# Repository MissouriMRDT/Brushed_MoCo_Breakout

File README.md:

# Brushed_MoCo_Breakout
Breakout board for custom brushed DC motor controllers

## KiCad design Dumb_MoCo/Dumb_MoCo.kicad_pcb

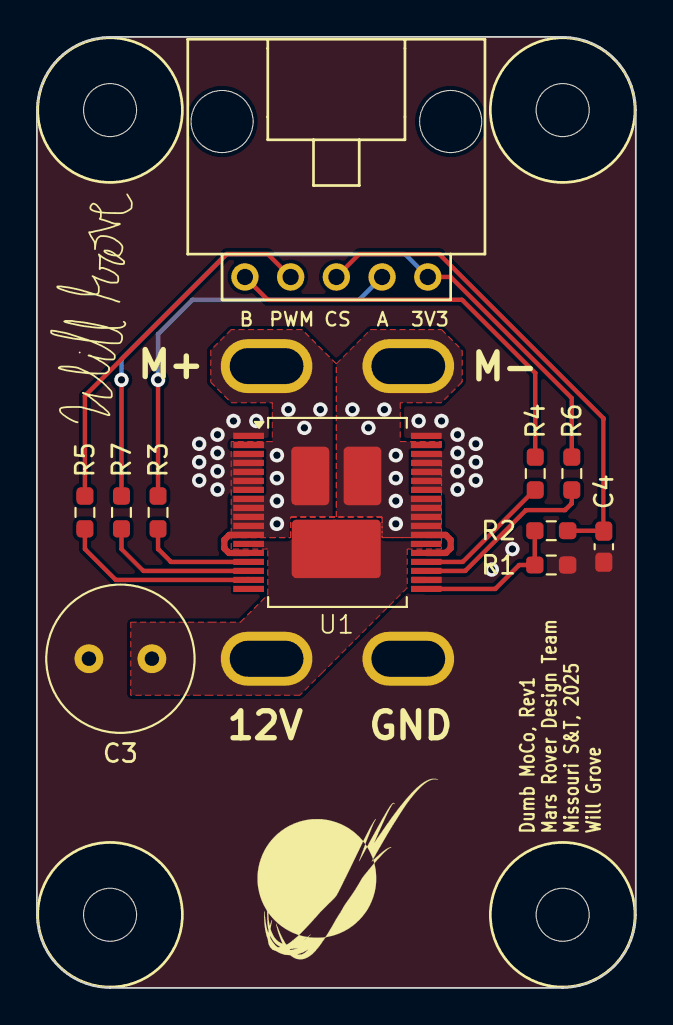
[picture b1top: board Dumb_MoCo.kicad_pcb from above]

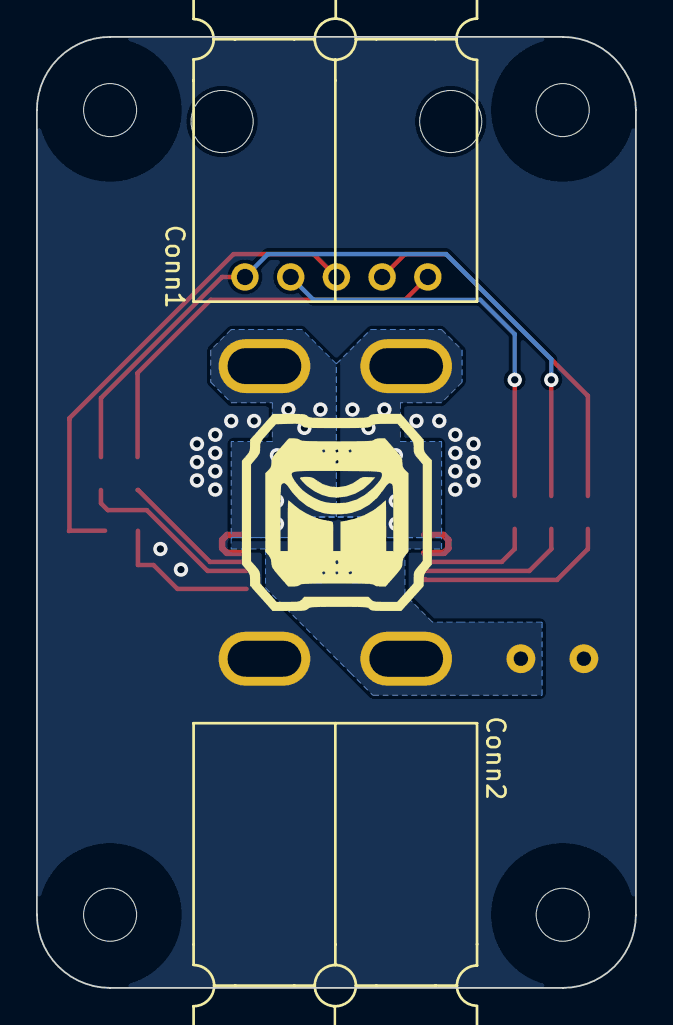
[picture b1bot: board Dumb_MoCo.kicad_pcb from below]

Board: 2 copper layers, 33.3 x 52.8 mm, 17 parts (2 on the bottom side), 15 nets.

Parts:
C3: 330uF; C_Radial_D8.0mm_H11.5mm_P3.50mm
C4: 33nF; C_0603_1608Metric_Pad1.08x0.95mm_HandSolder
Conn1, Conn2: AndersonPP; Square_Anderson_2_H_Side_By_Side
Conn3: Molex_SL_05; MOLEX_SL_05_Horizontal
H1, H2, H3, H4: MountingHole; 4_40_Hole
R1: 1.5k; R_0603_1608Metric_Pad0.98x0.95mm_HandSolder
R2: 10k; R_0603_1608Metric_Pad0.98x0.95mm_HandSolder
R3, R4, R5: 1k; R_0603_1608Metric_Pad0.98x0.95mm_HandSolder
R6, R7: 3.3k; R_0603_1608Metric_Pad0.98x0.95mm_HandSolder
U1: VNH5050A-E; ST_PowerSSO-36_TP

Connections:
+3V3: Conn3.5, R6.1, R7.1
+12V: C3.1, Conn2.2 (V+Log), U1.13 (VCC), U1.24 (VCC)
CS: C4.2, Conn3.3, R2.2
GND: C3.2, C4.1, Conn2.1 (GND), R1.2, U1.1 (GND_A), U1.3 (GND_A), U1.4 (GND_A), U1.5 (GND_A), U1.6 (GND_A), U1.7 (GND_A), U1.20 (CS_DIS), U1.30 (GND_B), U1.31 (GND_B), U1.32 (GND_B), U1.33 (GND_B), U1.34 (GND_B), U1.36 (GND_B)
IN_A: Conn3.4, R3.1
IN_B: Conn3.1, R4.1
unnamed: Conn1.1 (GND), U1.2 (OUT_A), U1.8 (OUT_A), U1.9 (OUT_A), U1.10 (OUT_A), U1.11 (OUT_A), U1.12 (OUT_A), U1.14 (OUT_A)
unnamed: Conn1.2 (V+Log), U1.23 (OUT_B), U1.25 (OUT_B), U1.26 (OUT_B), U1.27 (OUT_B), U1.28 (OUT_B), U1.29 (OUT_B), U1.35 (OUT_B)
unnamed: R1.1, R2.1, U1.19 (CS)
unnamed: R7.2, U1.16 (DIAG_A/EN_A)
unnamed: R6.2, U1.21 (DIAG_B/EN_B)
unnamed: R3.2, U1.15 (INA)
unnamed: R4.2, U1.22 (INB)
unnamed: R5.2, U1.17 (PWM)
PWM: Conn3.2, R5.1

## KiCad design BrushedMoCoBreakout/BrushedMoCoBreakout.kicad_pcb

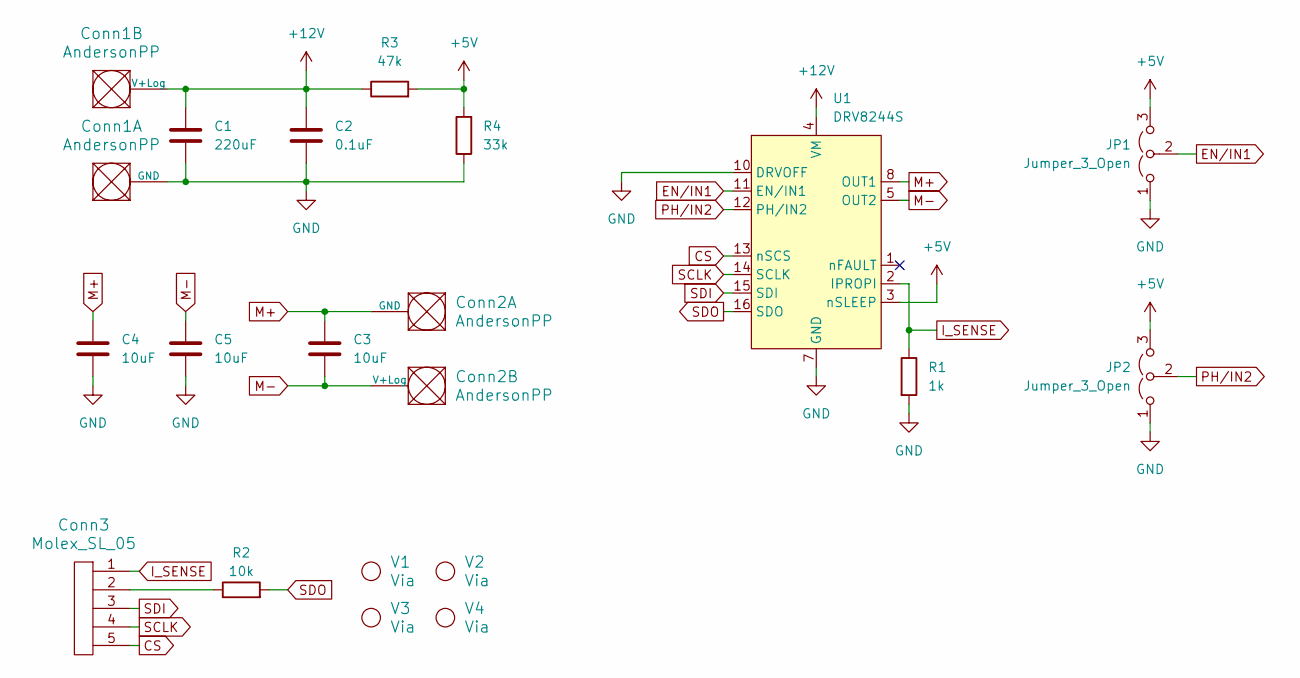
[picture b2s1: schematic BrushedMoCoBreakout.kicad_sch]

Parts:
C1: 220uF; CP_Radial_D6.3mm_P2.50mm
C2: 0.1uF; C_0603_1608Metric_Pad1.08x0.95mm_HandSolder
C3, C4, C5: 10uF; C_0603_1608Metric_Pad1.08x0.95mm_HandSolder
Conn1, Conn2: AndersonPP; Square_Anderson_2_H_Stacked_PV
Conn3: Molex_SL_05; MOLEX_SL_05_Horizontal
JP1, JP2: Jumper_3_Open; PinHeader_1x03_P1.00mm_Vertical
R1: 1k; R_0603_1608Metric_Pad0.98x0.95mm_HandSolder
R2: 10k; R_0603_1608Metric_Pad0.98x0.95mm_HandSolder
R3: 47k; R_0603_1608Metric_Pad0.98x0.95mm_HandSolder
R4: 33k; R_0603_1608Metric_Pad0.98x0.95mm_HandSolder
U1: DRV8244S; VQFN-HR-16_4.0mmx7.0mm_ThermalVias
V1, V2, V3, V4: Via; 4_40_Hole

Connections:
+5V: JP1.3 (B), JP2.3 (B), R3.2, R4.2, U1.3 (nSLEEP)
+12V: C1.1, C2.1, Conn1.2 (V+Log), R3.1, U1.4 (VM)
CS: Conn3.5, U1.13 (nSCS)
EN/IN1: JP1.2 (C), U1.11 (EN/IN1)
GND: C1.2, C2.2, C4.2, C5.2, Conn1.1 (GND), JP1.1 (A), JP2.1 (A), R1.2, R4.1, U1.7 (GND), U1.10 (DRVOFF)
I_SENSE: Conn3.1, R1.1, U1.2 (IPROPI)
M+: C3.1, C4.1, Conn2.1 (GND), U1.8 (OUT1), U1.9 (OUT1)
M-: C3.2, C5.1, Conn2.2 (V+Log), U1.5 (OUT2), U1.6 (OUT2)
unnamed: Conn3.2, R2.1
PH/IN2: JP2.2 (C), U1.12 (PH/IN2)
SCLK: Conn3.4, U1.14 (SCLK)
SDI: Conn3.3, U1.15 (SDI)
SDO: R2.2, U1.16 (SDO)

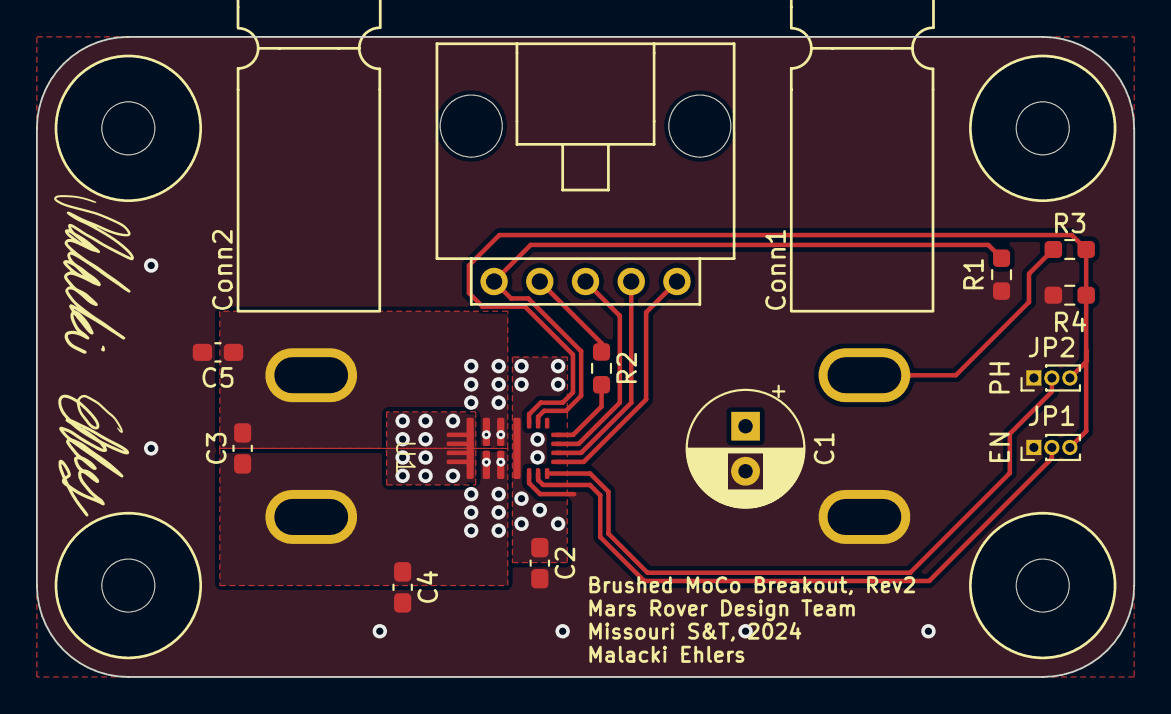
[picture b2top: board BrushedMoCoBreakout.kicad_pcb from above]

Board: 2 copper layers, 61.0 x 35.6 mm, 19 parts (0 on the bottom side), 13 nets.

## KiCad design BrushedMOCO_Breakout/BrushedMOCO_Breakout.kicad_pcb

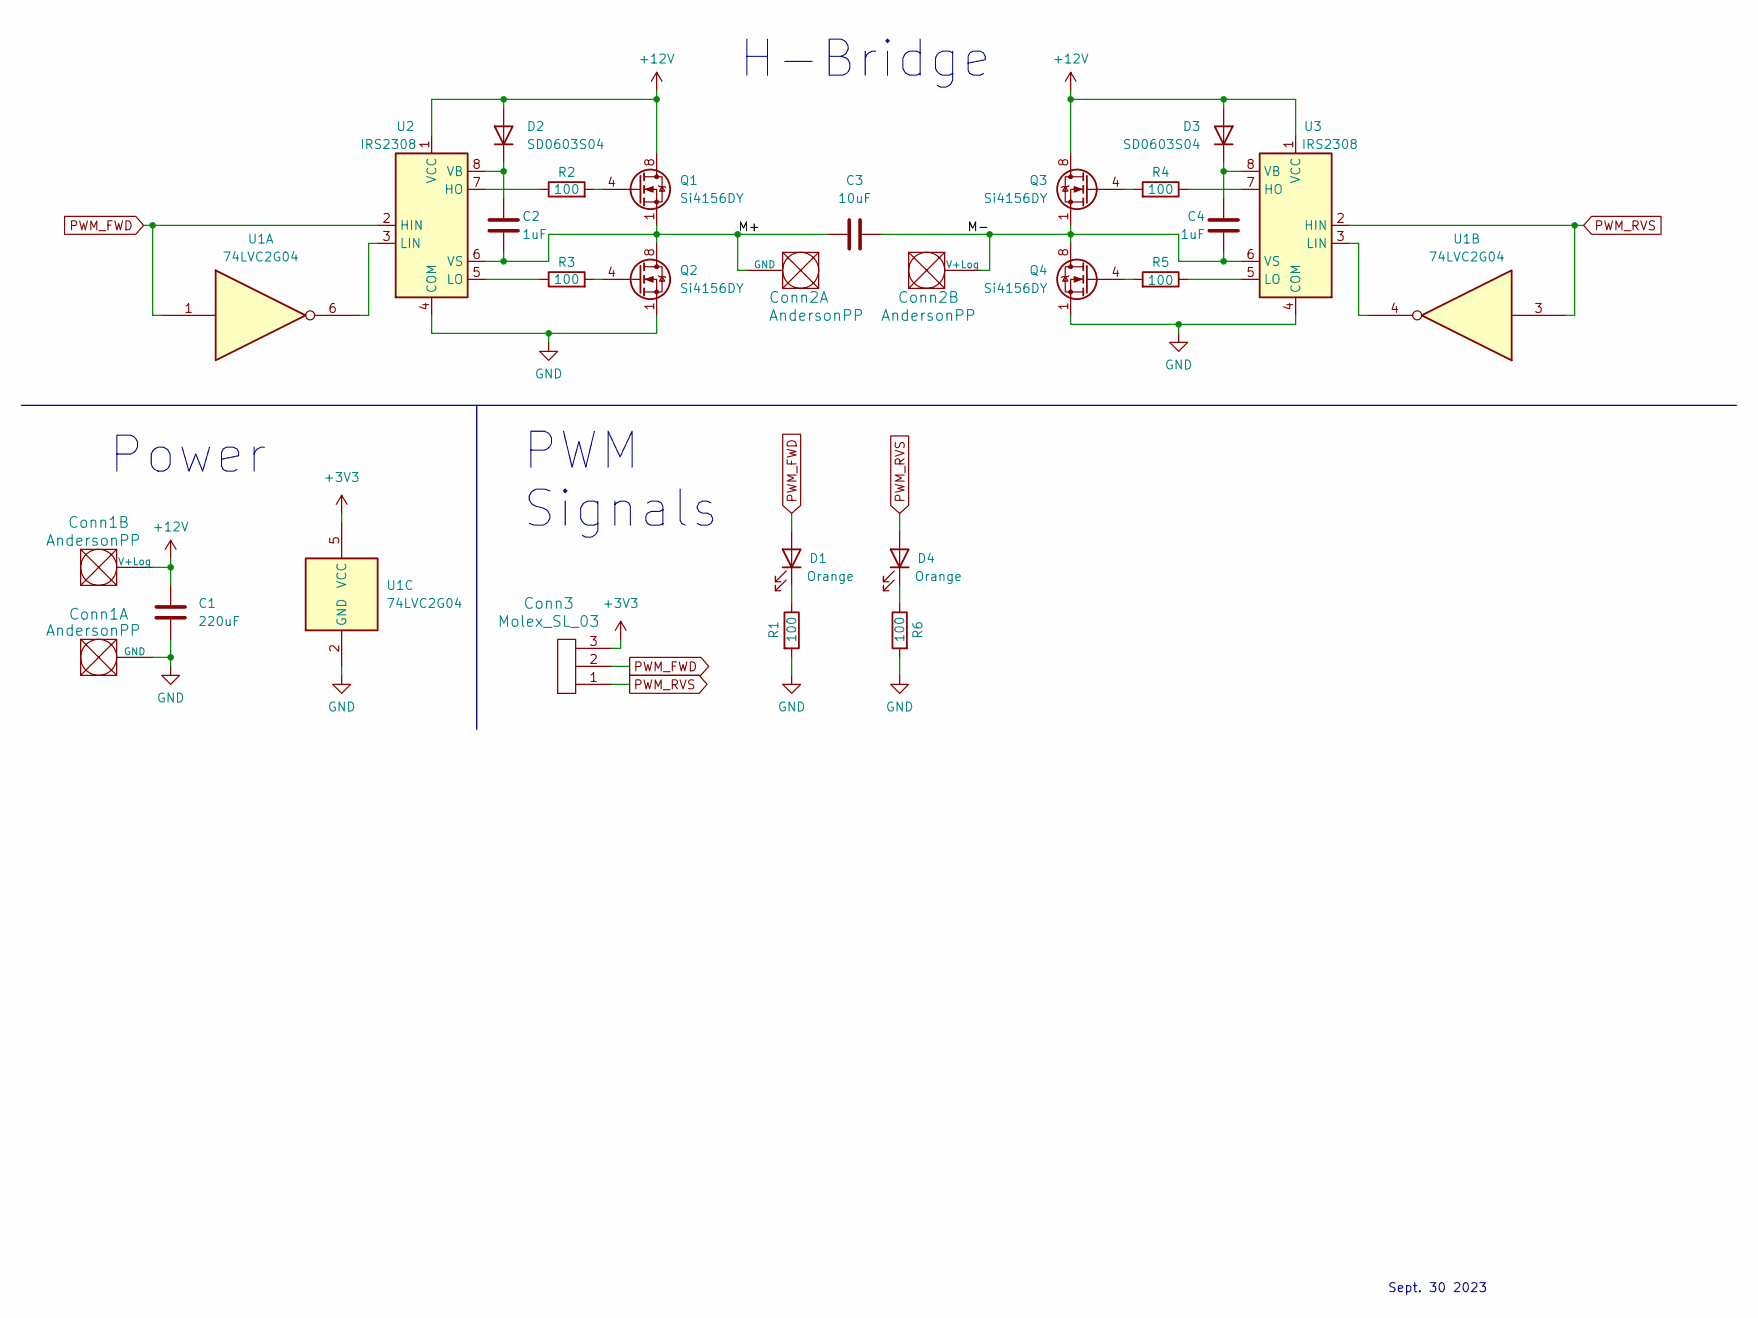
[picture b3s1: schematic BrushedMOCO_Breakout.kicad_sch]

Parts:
C1: 220uF; CP_Radial_D6.3mm_P2.50mm
C2, C4: 1uF; C_0603_1608Metric_Pad1.08x0.95mm_HandSolder
C3: 10uF; C_0603_1608Metric_Pad1.08x0.95mm_HandSolder
Conn1, Conn2: AndersonPP; Square_Anderson_2_H_Side_By_Side
Conn3: Molex_SL_03; MOLEX_SL_03_Horizontal
D1, D4: Orange; LED_0603_1608Metric_Pad1.05x0.95mm_HandSolder
D2, D3: SD0603S04; D_0603_1608Metric_Pad1.05x0.95mm_HandSolder
Q1, Q2, Q3, Q4: Si4156DY; SOIC-8_3.9x4.9mm_P1.27mm
R1, R2, R3, R4, R5, R6: 100; R_0603_1608Metric_Pad0.98x0.95mm_HandSolder
U1: 74LVC2G04; SOT-23-6_Handsoldering
U2, U3: IRS2308; SOIC-8_3.9x4.9mm_P1.27mm

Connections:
+3V3: Conn3.3, U1.5 (VCC)
+12V: C1.1, Conn1.2 (V+Log), D2.2 (A), D3.2 (A), Q1.5 (D), Q1.6 (D), Q1.7 (D), Q1.8 (D), Q3.5 (D), Q3.6 (D), Q3.7 (D), Q3.8 (D), U2.1 (VCC), U3.1 (VCC)
/M+: C2.2, C3.1, Conn2.1 (GND), Q1.1 (S), Q1.2 (S), Q1.3 (S), Q2.5 (D), Q2.6 (D), Q2.7 (D), Q2.8 (D), U2.6 (VS)
/M-: C3.2, C4.2, Conn2.2 (V+Log), Q3.1 (S), Q3.2 (S), Q3.3 (S), Q4.5 (D), Q4.6 (D), Q4.7 (D), Q4.8 (D), U3.6 (VS)
GND: C1.2, Conn1.1 (GND), Q2.1 (S), Q2.2 (S), Q2.3 (S), Q4.1 (S), Q4.2 (S), Q4.3 (S), R1.2, R6.2, U1.2 (GND), U2.4 (COM), U3.4 (COM)
unnamed: D1.1 (K), R1.1
unnamed: C2.1, D2.1 (K), U2.8 (VB)
unnamed: C4.1, D3.1 (K), U3.8 (VB)
unnamed: D4.1 (K), R6.1
unnamed: Q1.4 (G), R2.2
unnamed: Q2.4 (G), R3.2
unnamed: Q3.4 (G), R4.2
unnamed: Q4.4 (G), R5.2
unnamed: R2.1, U2.7 (HO)
unnamed: U1.6, U2.3 (LIN)
unnamed: R3.1, U2.5 (LO)
unnamed: R4.1, U3.7 (HO)
unnamed: U1.4, U3.3 (LIN)
unnamed: R5.1, U3.5 (LO)
PWM_FWD: Conn3.2, D1.2 (A), U1.1, U2.2 (HIN)
PWM_RVS: Conn3.1, D4.2 (A), U1.3, U3.2 (HIN)

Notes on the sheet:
PWM Signals
H-Bridge
Sept. 30 2023
Power

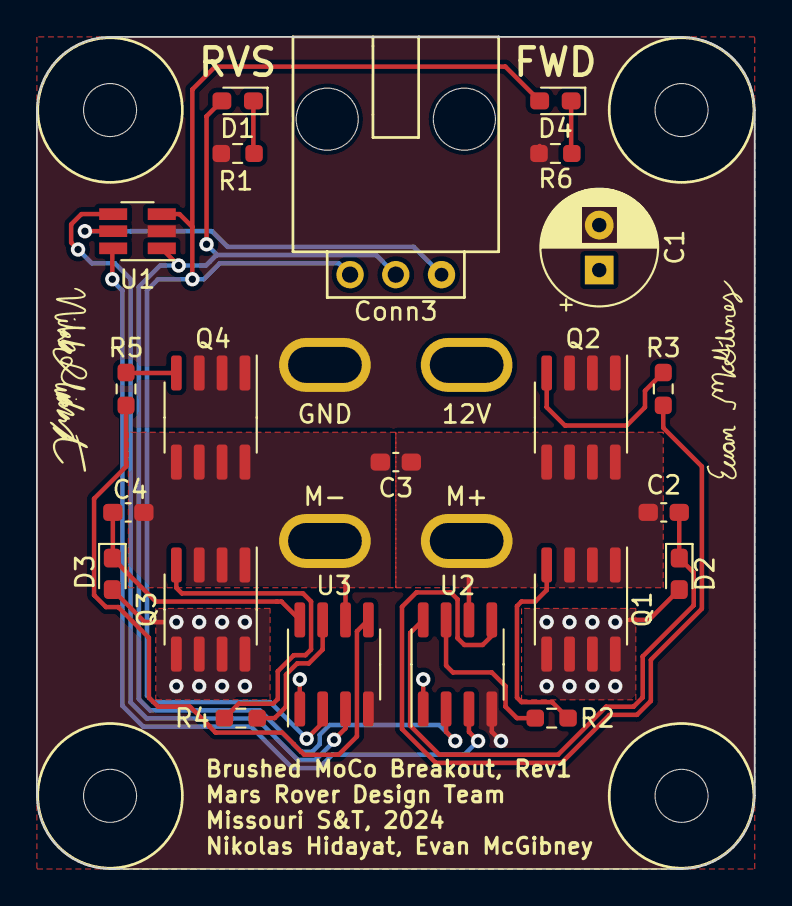
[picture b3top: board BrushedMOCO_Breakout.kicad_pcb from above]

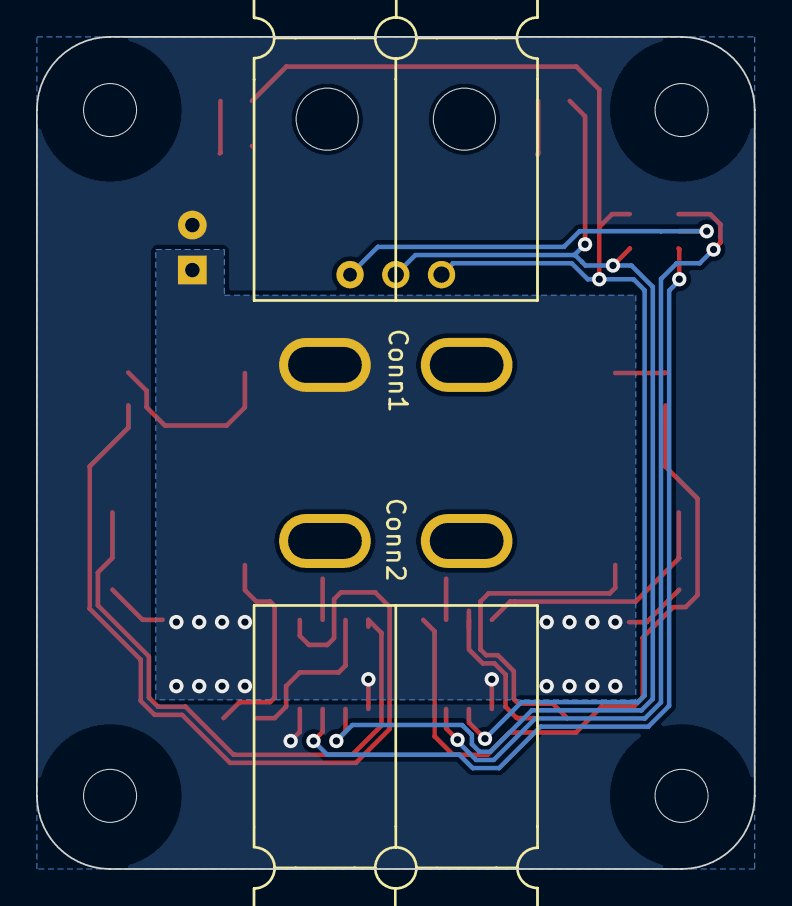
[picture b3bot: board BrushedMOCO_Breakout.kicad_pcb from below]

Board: 2 copper layers, 39.9 x 46.2 mm, 24 parts (2 on the bottom side), 21 nets.

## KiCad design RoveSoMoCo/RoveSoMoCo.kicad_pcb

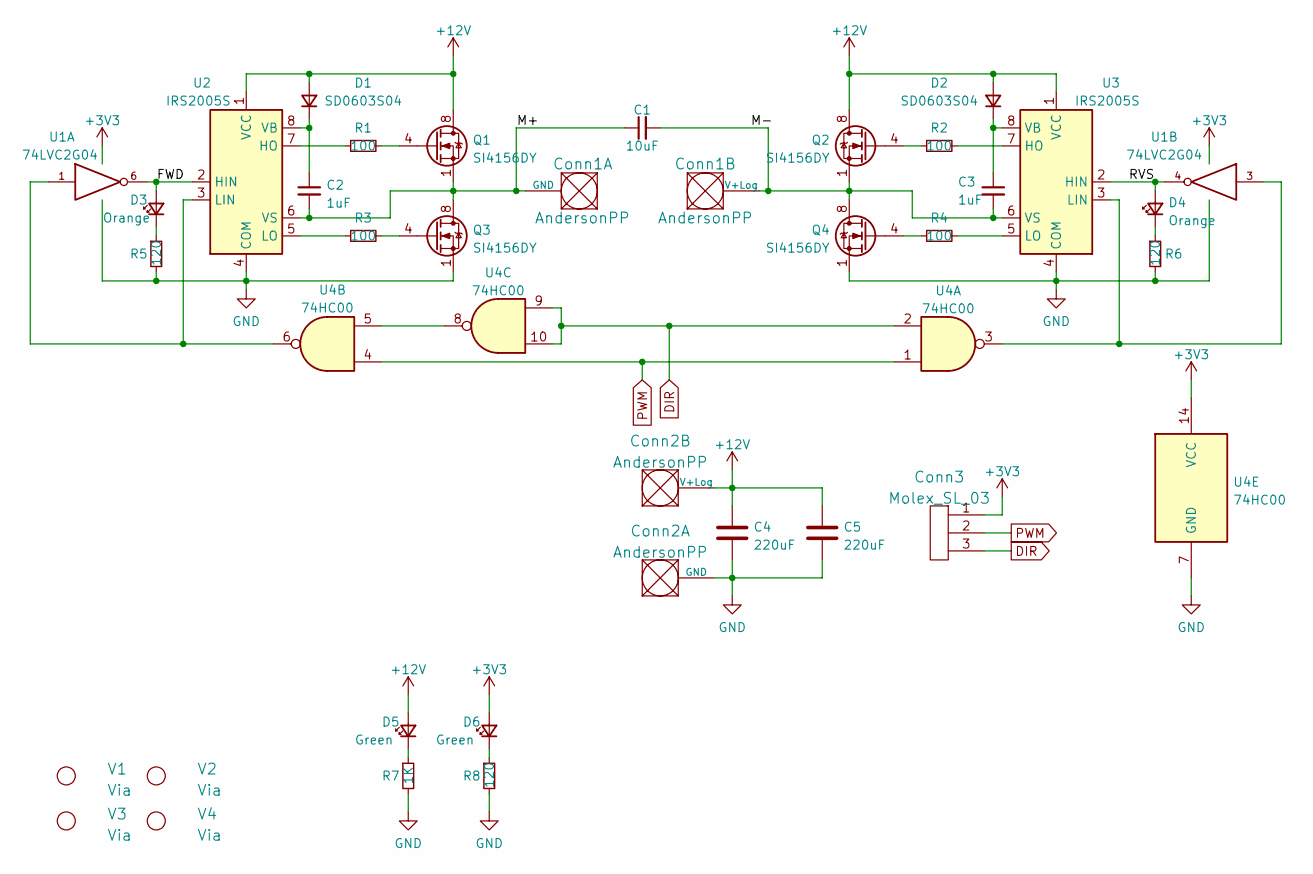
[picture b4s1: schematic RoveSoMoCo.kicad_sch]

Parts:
C1: 10uF; C_0603_1608Metric_Pad1.08x0.95mm_HandSolder
C2, C3: 1uF; C_0603_1608Metric_Pad1.08x0.95mm_HandSolder
C4, C5: 220uF; CP_Radial_D6.3mm_P2.50mm
Conn1, Conn2: AndersonPP; Square_Anderson_2_H_Side_By_Side
Conn3: Molex_SL_03; MOLEX_SL_03_Vertical
D1, D2: SD0603S04; D_0603_1608Metric_Pad1.05x0.95mm_HandSolder
D3, D4: Orange; LED_0603_1608Metric_Pad1.05x0.95mm_HandSolder
D5, D6: Green; LED_0603_1608Metric_Pad1.05x0.95mm_HandSolder
Q1, Q2, Q3, Q4: SI4156DY; SOIC-8_3.9x4.9mm_P1.27mm
R1, R2, R3, R4: 100; R_0603_1608Metric_Pad0.98x0.95mm_HandSolder
R5, R6, R8: 120; R_0603_1608Metric_Pad0.98x0.95mm_HandSolder
R7: 1K; R_0603_1608Metric_Pad0.98x0.95mm_HandSolder
U1: 74LVC2G04; SOT-23-6_Handsoldering
U2, U3: IRS2005S; SOIC-8_3.9x4.9mm_P1.27mm
U4: 74HC00; SO-14_5.3x10.2mm_P1.27mm
V1, V2, V3, V4: Via; 4_40_Hole_Corner

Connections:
+3V3: Conn3.1, D6.2 (A), U1.5 (VCC), U4.14 (VCC)
+12V: C4.1, C5.1, Conn2.2 (V+Log), D1.2 (A), D2.2 (A), D5.2 (A), Q1.5 (D), Q1.6 (D), Q1.7 (D), Q1.8 (D), Q2.5 (D), Q2.6 (D), Q2.7 (D), Q2.8 (D), U2.1 (VCC), U3.1 (VCC)
/FWD: D3.2 (A), U1.6, U2.2 (HIN)
/M+: C1.1, C2.2, Conn1.1 (GND), Q1.1 (S), Q1.2 (S), Q1.3 (S), Q3.5 (D), Q3.6 (D), Q3.7 (D), Q3.8 (D), U2.6 (VS)
/M-: C1.2, C3.2, Conn1.2 (V+Log), Q2.1 (S), Q2.2 (S), Q2.3 (S), Q4.5 (D), Q4.6 (D), Q4.7 (D), Q4.8 (D), U3.6 (VS)
/RVS: D4.2 (A), U1.4, U3.2 (HIN)
DIR: Conn3.3, U4.2, U4.9, U4.10
GND: C4.2, C5.2, Conn2.1 (GND), Q3.1 (S), Q3.2 (S), Q3.3 (S), Q4.1 (S), Q4.2 (S), Q4.3 (S), R5.2, R6.2, R7.2, R8.2, U1.2 (GND), U2.4 (COM), U3.4 (COM), U4.7 (GND)
unnamed: C2.1, D1.1 (K), U2.8 (VB)
unnamed: C3.1, D2.1 (K), U3.8 (VB)
unnamed: D3.1 (K), R5.1
unnamed: D4.1 (K), R6.1
unnamed: D5.1 (K), R7.1
unnamed: D6.1 (K), R8.1
unnamed: Q1.4 (G), R1.2
unnamed: Q2.4 (G), R2.1
unnamed: Q3.4 (G), R3.2
unnamed: Q4.4 (G), R4.1
unnamed: R1.1, U2.7 (HO)
unnamed: R2.2, U3.7 (HO)
unnamed: R3.1, U2.5 (LO)
unnamed: R4.2, U3.5 (LO)
unnamed: U1.1, U2.3 (LIN), U4.6
unnamed: U1.3, U3.3 (LIN), U4.3
unnamed: U4.5, U4.8
PWM: Conn3.2, U4.1, U4.4

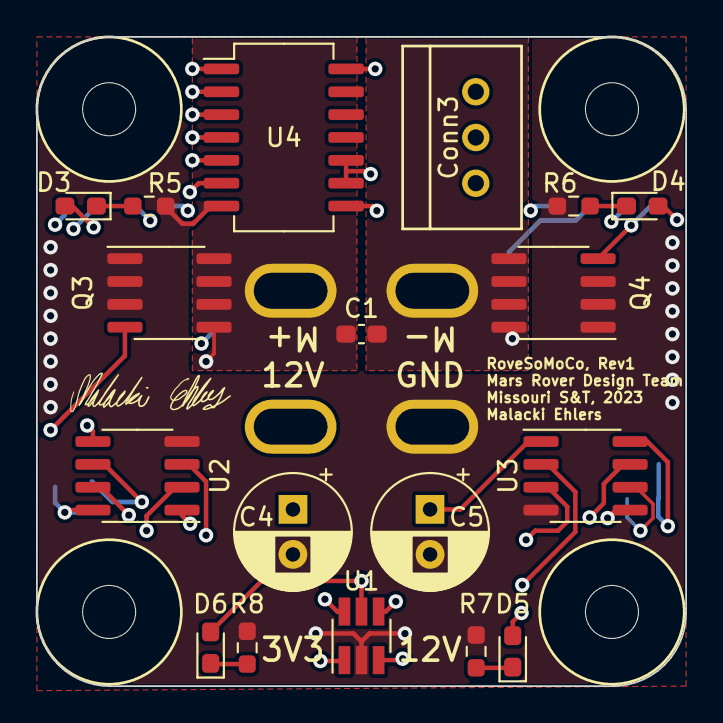
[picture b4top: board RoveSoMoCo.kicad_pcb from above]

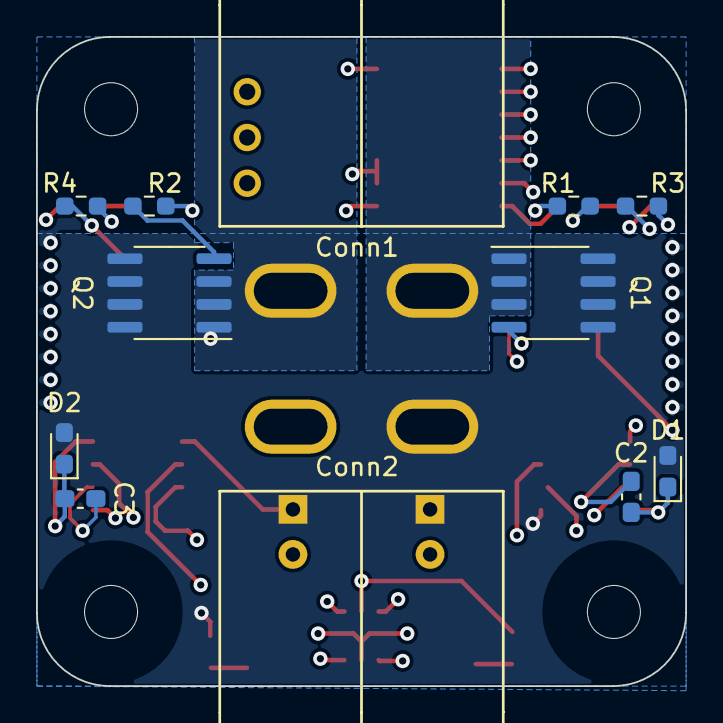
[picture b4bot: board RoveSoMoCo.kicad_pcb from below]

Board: 4 copper layers, 36.1 x 36.1 mm, 34 parts (12 on the bottom side), 26 nets.

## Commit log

2023-03-08 Switch to 4-layer
2023-03-09 Increased size of board and planes
2023-03-21 generated gerbs
2023-03-21 Added header and signature
2023-03-21 generated gerbs (again)
2023-09-16 Created file path
2023-09-16 imported tiensy symbol
2023-09-16 added ethernet
2023-09-21 Schematic Created
2023-09-25 Circuit improvements
2023-09-27 Some Schematic Review Adjustments
2023-09-30 Most of Schematic Review Adjustments
    This should be all of the schematic review adjustments except for the footprints for the IRS2308. I wasn't sure whether to use
    Package_DFN_QFN:Infineon_MLPQ-48-1EP_7x7mm_P0.5mm_EP5.55x5.55mm
    or
    Package_DFN_QFN:Infineon_MLPQ-48-1EP_7x7mm_P0.5mm_EP5.15x5.15mm
2023-10-03 Finished Footprints
2023-10-03 cleaned up lines
2023-10-15 Saving PCB Progress
2023-10-15 Niko's Signature Added
2023-10-17 obscenely rough draft
    sorry, this one may hurt to look at
2023-10-17 A general outline of where stuff should go
2023-10-17 Some adjustments
2023-10-17 save progress
2023-10-17 Signatures added
2023-10-18 labels added
2023-10-21 Made step file
2023-11-05 Adjustments
    Fixed track width, moved Q2,Q3 further from the mounting holes, reduced vertical space between Andersons, moved some labels
2023-11-06 Finish layout for order
2023-11-06 Generate Gerbs
2024-02-22 Wipe old files
2024-02-27 Initial design
2024-02-28 Swap to square andersons
2024-02-28 Adjust resistor values
2024-02-28 Add signature
2024-09-07 Added Dumb MoCo KiCAD files
2024-09-15 Completed layout before review
2024-09-15 Rearranged res, added silkscreenssss
2024-09-22 Removed C1
2024-09-26 Added Chamber Ult Silkscreen
2024-09-28 Started on layout
2024-09-29 Finished layout draft
    made anderson and SL vertical
2024-09-30 Updated silkscreen
2024-09-30 Added vias and made 12V plane wider
2024-09-30 Adjusted vias
2024-09-30 more vias
2024-10-04 Flipped VNH and reordered SL
2024-10-04 Reordered SL
2024-10-04 Flipped VNH
2024-10-23 Swapped for new VNH IC
2024-10-26 Started new VNH layout
2024-10-26 Added vias and changed bulk cap
2024-10-27 Fixed GND plane island
2024-10-28 Moved up vias, connected pads with fat trace
2024-10-28 Added silkscreens
2024-10-29 Gerbs generated
2024-10-31 Zipped Gerbs
2024-11-01 Added drill files
2024-11-08 Changed Bulk cap to 330uF
